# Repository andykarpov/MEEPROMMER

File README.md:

MEEPROMMER
==========

(E)EPROM programmer based on Arduino hardware

The MEEPROMMER is a combination of hardware and software that lets you read and write 
data from (and to) 28C256, 28C128, 28C64, 28C16 EEPROMS.

The Arduino firmware provides a serial interface with simple commands to transfer data 
between a host computer and an eeprom.

For the host computer a Java based GUI application is available that uses the RXTX 
library to interface the programmer.

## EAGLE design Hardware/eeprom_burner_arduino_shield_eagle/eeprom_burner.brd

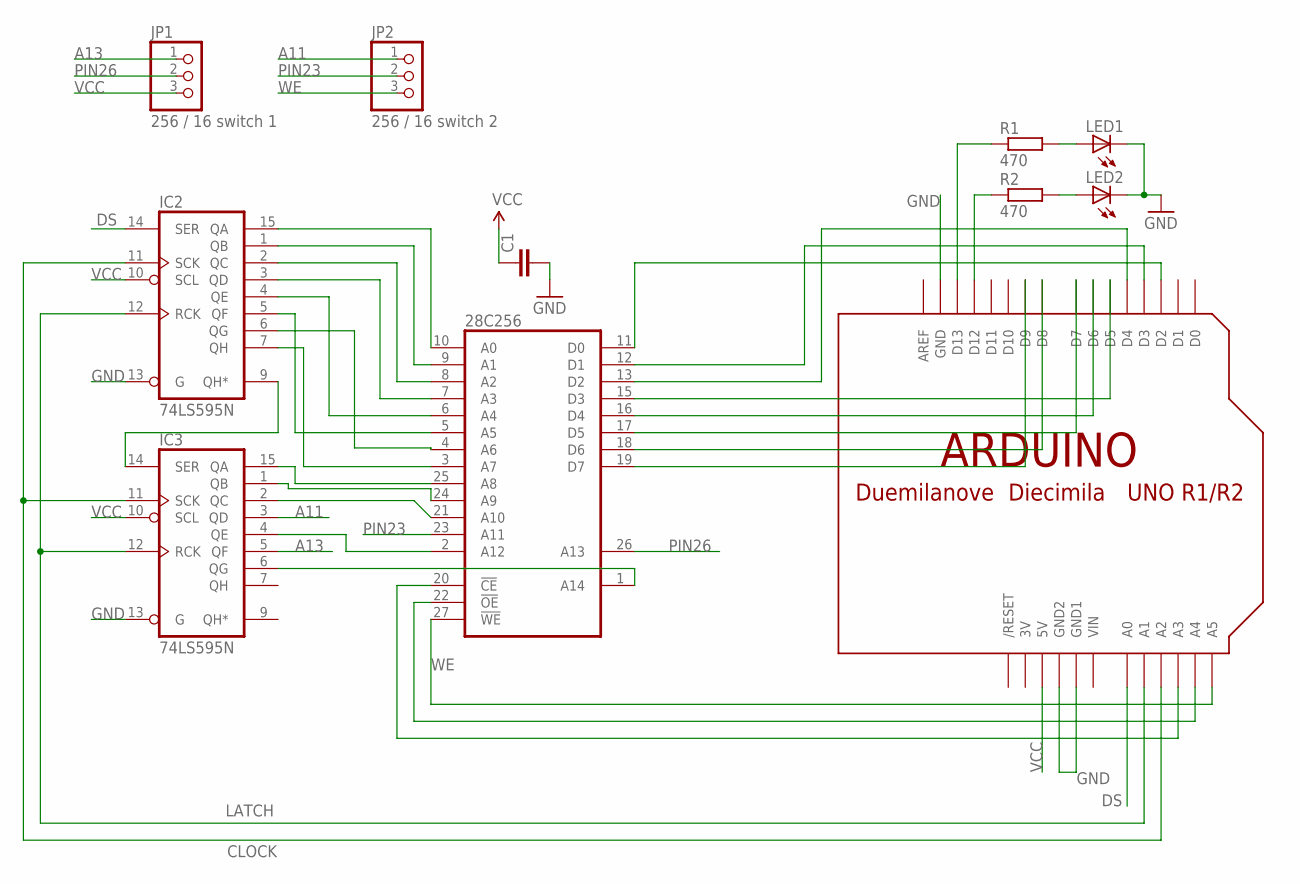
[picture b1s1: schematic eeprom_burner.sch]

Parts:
28C256: 2864; DIL28
C1: CAPPTH; CAP-PTH-SMALL
IC2, IC3: 74LS595N; DIL16
JP1: 256 / 16 switch 1; 1X03
JP2: 256 / 16 switch 2; 1X03
LED1, LED2: LED3MM
R1, R2: 470; 0204/7
U$1: ARDUINO-NODIM

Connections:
3V: U$1.3V
A11: IC3.3 (QD), JP2.1
A13: IC3.5 (QF), JP1.1
CLOCK: IC2.11 (SCK), IC3.11 (SCK), U$1.A2
DS: IC2.14 (SER), U$1.A0
GND: 28C256.14 (GND), C1.2, IC2.8 (GND), IC2.13 (G), IC3.8 (GND), IC3.13 (G), LED1.K (C), LED2.K (C), U$1.GND, U$1.GND1, U$1.GND2
LATCH: IC2.12 (RCK), IC3.12 (RCK), U$1.A1
unnamed: R2.1, U$1.D12
unnamed: 28C256.22 (!OE), U$1.A4
unnamed: 28C256.20 (!CE), U$1.A3
unnamed: 28C256.11 (D0), U$1.D2
unnamed: 28C256.12 (D1), U$1.D3
unnamed: 28C256.13 (D2), U$1.D4
unnamed: 28C256.15 (D3), U$1.D5
unnamed: 28C256.16 (D4), U$1.D6
unnamed: 28C256.17 (D5), U$1.D7
unnamed: 28C256.18 (D6), U$1.D8
unnamed: 28C256.19 (D7), U$1.D9
unnamed: 28C256.10 (A0), IC2.15 (QA)
unnamed: 28C256.9 (A1), IC2.1 (QB)
unnamed: 28C256.8 (A2), IC2.2 (QC)
unnamed: 28C256.7 (A3), IC2.3 (QD)
unnamed: 28C256.6 (A4), IC2.4 (QE)
unnamed: 28C256.5 (A5), IC2.5 (QF)
unnamed: 28C256.4 (A6), IC2.6 (QG)
unnamed: 28C256.3 (A7), IC2.7 (QH)
unnamed: IC2.9 (QH*), IC3.14 (SER)
unnamed: 28C256.25 (A8), IC3.15 (QA)
unnamed: 28C256.24 (A9), IC3.1 (QB)
unnamed: 28C256.21 (A10), IC3.2 (QC)
unnamed: R1.1, U$1.D13
unnamed: 28C256.2 (A12), IC3.4 (QE)
unnamed: LED1.A, R1.2
unnamed: 28C256.1 (A14), IC3.6 (QG)
unnamed: LED2.A, R2.2
PIN23: 28C256.23 (A11), JP2.2
PIN26: 28C256.26 (A13), JP1.2
VCC: 28C256.28 (VCC), C1.1, IC2.10 (SCL), IC2.16 (VCC), IC3.10 (SCL), IC3.16 (VCC), JP1.3, U$1.5V
VIN: U$1.VIN
WE: 28C256.27 (!WE), JP2.3, U$1.A5

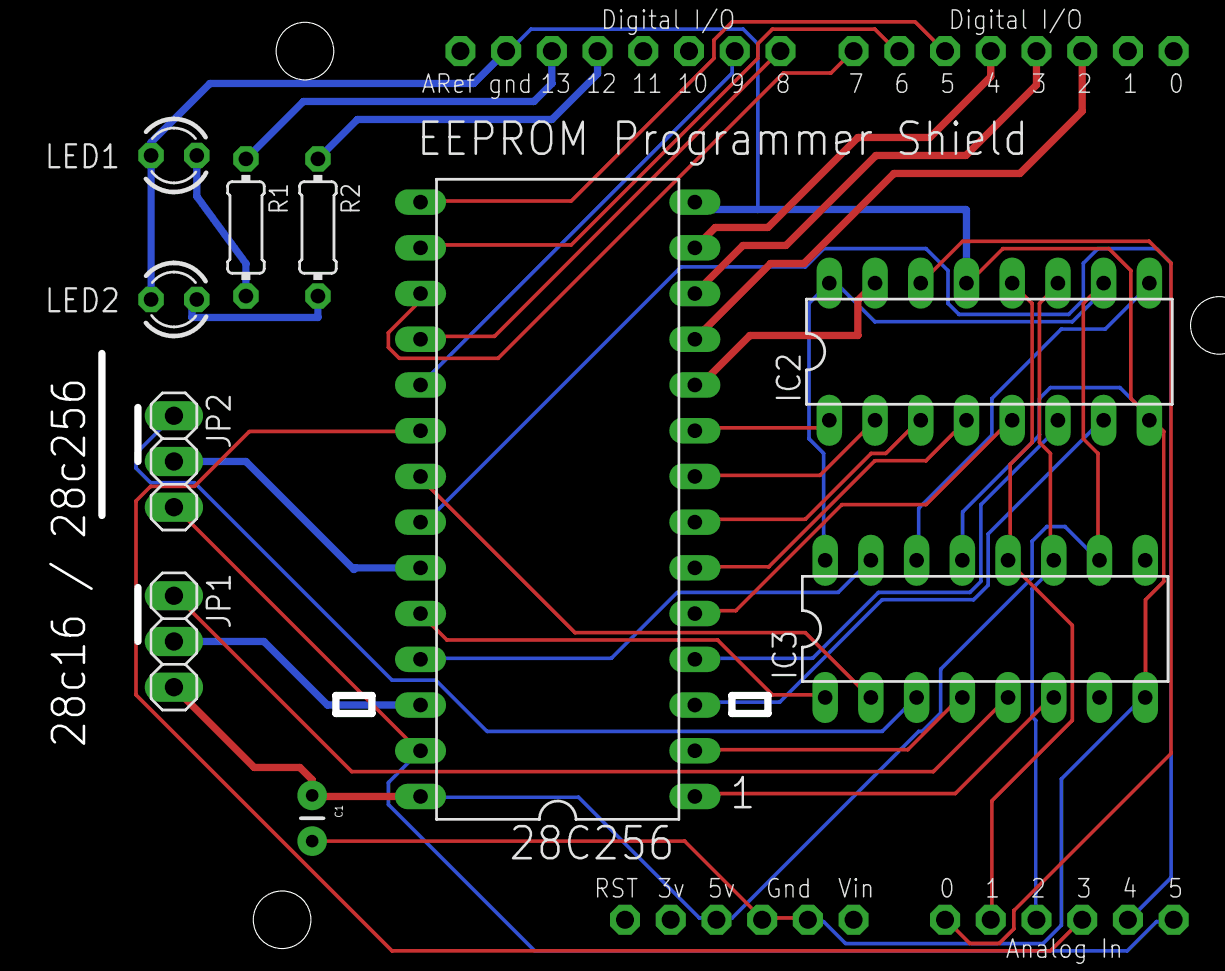
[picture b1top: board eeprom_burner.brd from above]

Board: 2 copper layers, 11 parts (0 on the bottom side), 38 nets.

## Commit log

2013-07-31 Added support for 27SF512 Speed improvements Cosmetic improvements "Run Sequence" support
2013-08-02 Fixed write data bit shift for Leonardo.
    Boost PWM now working on both UNO and Leonardo at 62kHz.
2013-08-02 Add additional comments to Arduino sketch also make chartohex a const
2013-08-02 Change form layout for better cross-platform compatability
2013-08-02 fixed
2013-08-03 Modified form for better layout on small screens (e.g. 1024x600)
2013-08-03 Fix potential bug for 28C page write
2013-08-05 Remove "always on top" for main form
2013-11-22 CMD list in version string corrected; matches parseCommand().
2013-11-22 New 'A,0000' command sets address bus to given value.
    Useful for debugging shift-register wiring and the resulting address bus
    byte order.
    e.g. `A,00FF` should only set A0..A7 high.
2014-09-12 Added support for 27C16; Hotfixes to work on OSX 10.6 and old Arduinos
2014-09-12 fixed netbeans build on older v6.9
2014-09-12 removed build from gitignore
2014-09-12 Added release
2014-09-13 updated board layout

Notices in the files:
parts and their libraries:
SparkFun: Licensing: CC v3.0 Share-Alike You are welcome to use this library for commercial purposes.
